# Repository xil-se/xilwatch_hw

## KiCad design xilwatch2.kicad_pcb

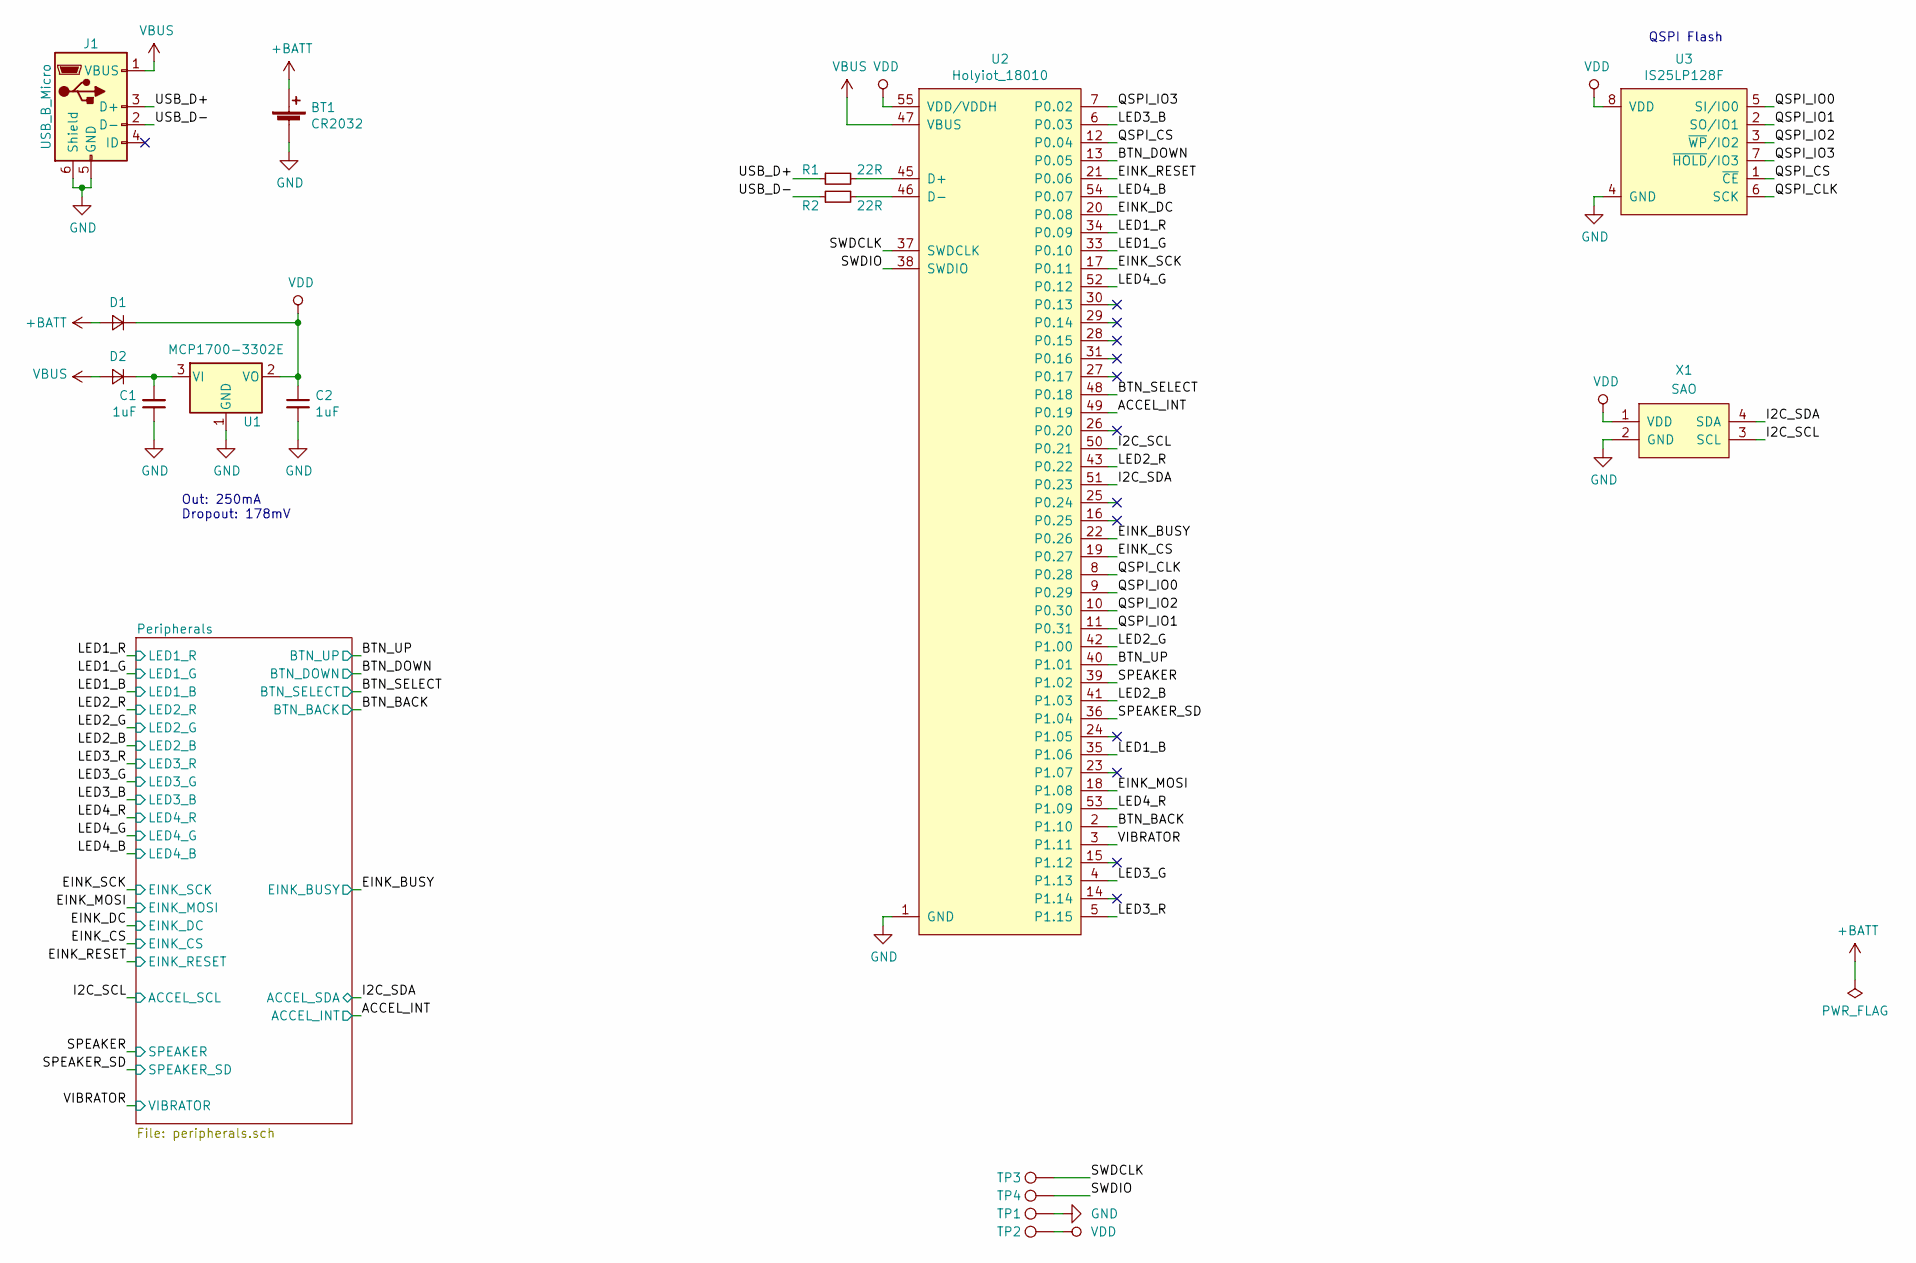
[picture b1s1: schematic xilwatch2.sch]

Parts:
BT1: CR2032; BAT-HLD-001
C1, C2: 1uF; C_0603_1608Metric
D1, D2: S1JHE; D_SOD-323F
J1: USB_B_Micro; USB_Micro-B_Molex-105017-0001
R1, R2: 22R; R_0603_1608Metric
TP1: TP_GND; TestPoint_Pad_D1.0mm
TP2: TP_VDD; TestPoint_Pad_D1.0mm
TP3: TP_SWDCLK; TestPoint_Pad_D1.0mm
TP4: TP_SWDIO; TestPoint_Pad_D1.0mm
U1: MCP1700-3302E; SOT-23
U2: Holyiot_18010
U3: IS25LP128F; WSON-8-1EP_6x5mm_P1.27mm_EP3.4x4mm
X1: SAO; SAO-2x2

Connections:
+BATT: BT1.1 (+), D1.2 (A)
/ACCEL_INT: U2.49 (P0.19); also elsewhere on the board
/BTN_BACK: U2.2 (P1.10); also elsewhere on the board
/BTN_DOWN: U2.13 (P0.05); also elsewhere on the board
/BTN_SELECT: U2.48 (P0.18); also elsewhere on the board
/BTN_UP: U2.40 (P1.01); also elsewhere on the board
/EINK_BUSY: U2.22 (P0.26); also elsewhere on the board
/EINK_CS: U2.19 (P0.27); also elsewhere on the board
/EINK_DC: U2.20 (P0.08); also elsewhere on the board
/EINK_MOSI: U2.18 (P1.08); also elsewhere on the board
/EINK_RESET: U2.21 (P0.06); also elsewhere on the board
/EINK_SCK: U2.17 (P0.11); also elsewhere on the board
/I2C_SCL: U2.50 (P0.21), X1.3 (SCL); also elsewhere on the board
/I2C_SDA: U2.51 (P0.23), X1.4 (SDA); also elsewhere on the board
/LED1_B: U2.35 (P1.06); also elsewhere on the board
/LED1_G: U2.33 (P0.10); also elsewhere on the board
/LED1_R: U2.34 (P0.09); also elsewhere on the board
/LED2_B: U2.41 (P1.03); also elsewhere on the board
/LED2_G: U2.42 (P1.00); also elsewhere on the board
/LED2_R: U2.43 (P0.22); also elsewhere on the board
/LED3_B: U2.6 (P0.03); also elsewhere on the board
/LED3_G: U2.4 (P1.13); also elsewhere on the board
/LED3_R: U2.5 (P1.15); also elsewhere on the board
/LED4_B: U2.54 (P0.07); also elsewhere on the board
/LED4_G: U2.52 (P0.12); also elsewhere on the board
/LED4_R: U2.53 (P1.09); also elsewhere on the board
/QSPI_CLK: U2.8 (P0.28), U3.6 (SCK)
/QSPI_CS: U2.12 (P0.04), U3.1 (~CE~)
/QSPI_IO0: U2.9 (P0.29), U3.5 (SI/IO0)
/QSPI_IO1: U2.11 (P0.31), U3.2 (SO/IO1)
/QSPI_IO2: U2.10 (P0.30), U3.3 (~WP~/IO2)
/QSPI_IO3: U2.7 (P0.02), U3.7 (~HOLD~/IO3)
/SPEAKER: U2.39 (P1.02); also elsewhere on the board
/SPEAKER_SD: U2.36 (P1.04); also elsewhere on the board
/SWDCLK: TP3.1, U2.37 (SWDCLK)
/SWDIO: TP4.1, U2.38 (SWDIO)
/USB_D+: J1.3 (D+), R1.1
/USB_D-: J1.2 (D-), R2.1
/VIBRATOR: U2.3 (P1.11); also elsewhere on the board
GND: BT1.2 (-), C1.1, C2.2, J1.5 (GND), J1.6 (Shield), TP1.1, U1.1 (GND), U2.1 (GND), U2.32 (GND), U2.44 (GND), U3.4 (GND), U3.9 (GND), X1.2 (GND); also elsewhere on the board
unnamed: C1.2, D2.1 (K), U1.3 (VI)
unnamed: R1.2, U2.45 (D+)
unnamed: R2.2, U2.46 (D-)
VBUS: D2.2 (A), J1.1 (VBUS), U2.47 (VBUS)
VDD: C2.1, D1.1 (K), TP2.1, U1.2 (VO), U2.55 (VDD/VDDH), U3.8 (VDD), X1.1 (VDD); also elsewhere on the board

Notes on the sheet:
Out: 250mA Dropout: 178mV
QSPI Flash

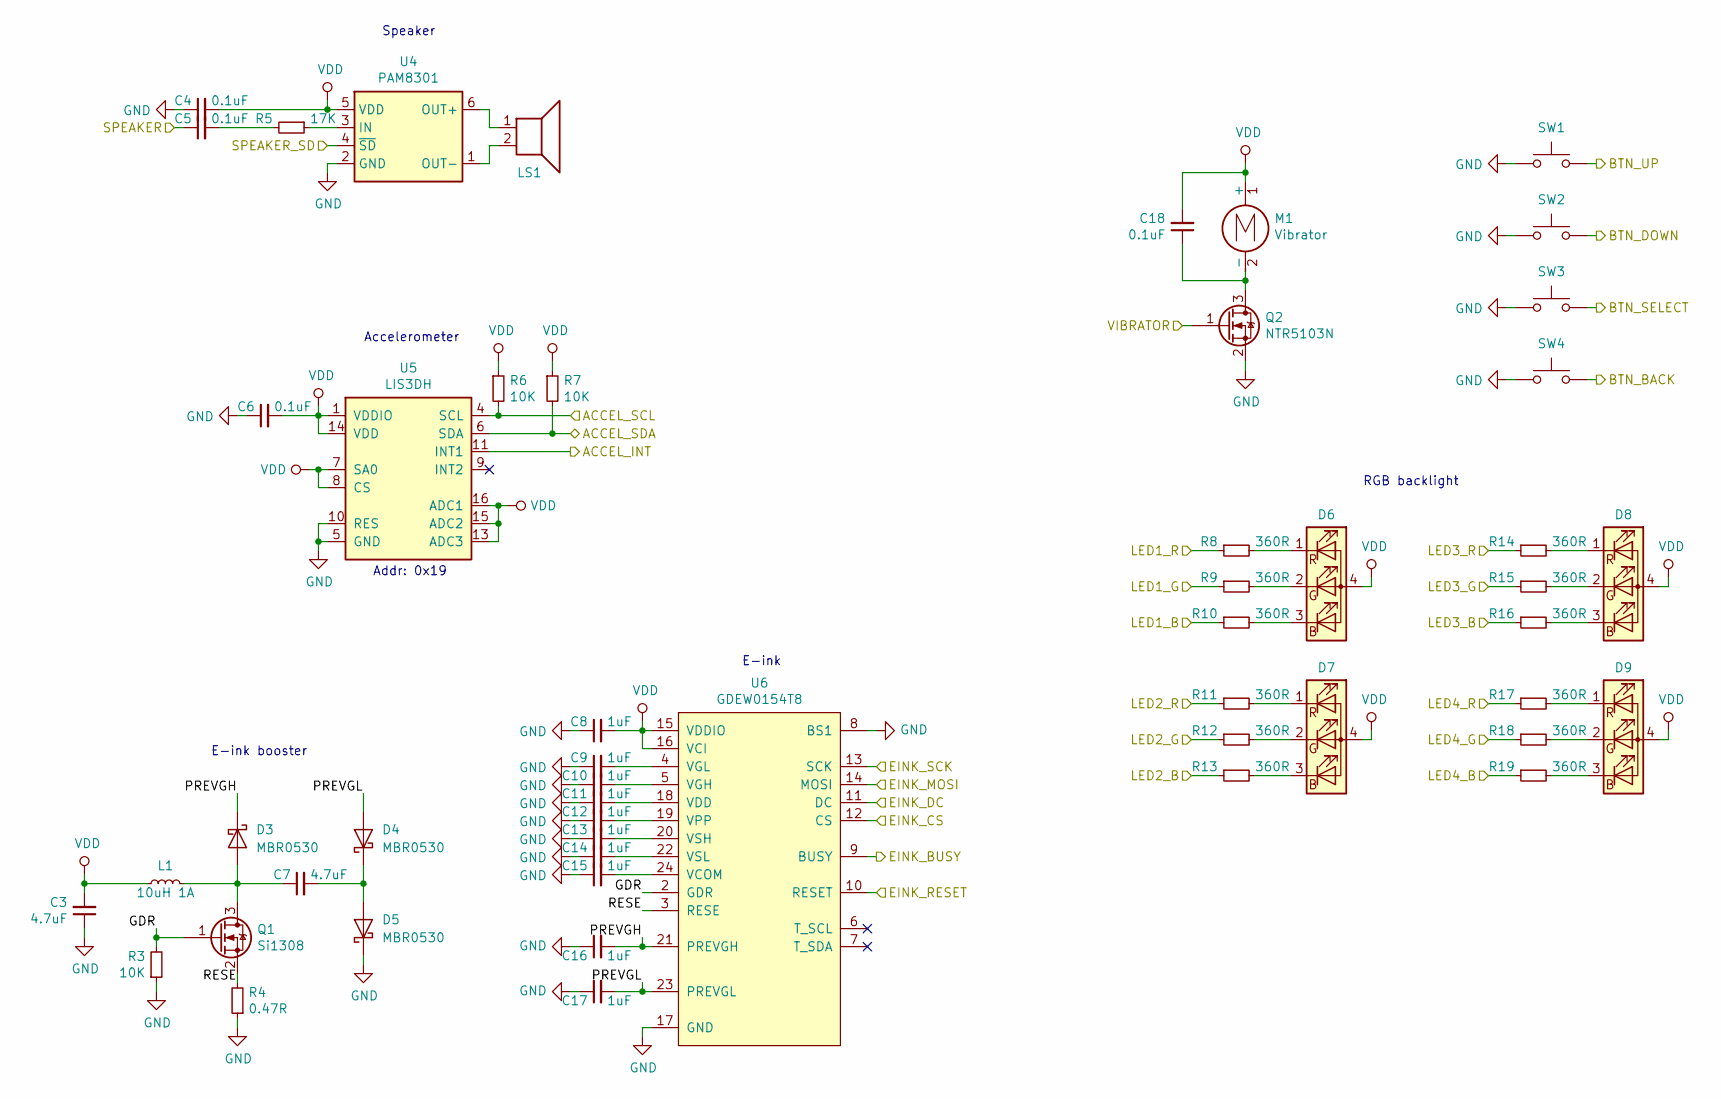
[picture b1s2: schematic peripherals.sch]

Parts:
C3, C7: 4.7uF; C_0603_1608Metric
C4, C5, C6, C18: 0.1uF; C_0603_1608Metric
C8, C9, C10, C11, C12, C13, C14, C15, C16, C17: 1uF; C_0603_1608Metric
D3, D4, D5: MBR0530; D_SOD-123
D6: LED_TopLeft; LED_RGBA_0606
D7: LED_TopRight; LED_RGBA_0606
D8: LED_BottomLeft; LED_RGBA_0606
D9: LED_BottomRight; LED_RGBA_0606
L1: 10uH 1A; L_Taiyo-Yuden_MD-3030; Part AISC-1210HS-100K-T2
LS1: CMT-5023S-SMT; CMT-5023S
M1: Vibrator; C1026B
Q1: Si1308; SOT-23
Q2: NTR5103N; SOT-23
R3, R6, R7: 10K; R_0603_1608Metric
R4: 0.47R; R_0603_1608Metric
R5: 17K; R_0603_1608Metric
R8, R9, R10, R11, R12, R13, R14, R15, R16, R17, R18, R19: 360R; R_0603_1608Metric
SW1: Btn_Up; KLS7-TS2402
SW2: Btn_Down; KLS7-TS2402
SW3: Btn_Select; KLS7-TS2402
SW4: Btn_Back; KLS7-TS2402
U4: PAM8301; SOT-23-6
U5: LIS3DH; LGA-16_3x3mm_P0.5mm_LayoutBorder3x5y
U6: GDEW0154T8; GoodDisplay_24P-0.5SH_1x24-Horizontal

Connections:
/ACCEL_INT: U5.11 (INT1); also elsewhere on the board
/BTN_BACK: SW4.2; also elsewhere on the board
/BTN_DOWN: SW2.2; also elsewhere on the board
/BTN_SELECT: SW3.2; also elsewhere on the board
/BTN_UP: SW1.2; also elsewhere on the board
/EINK_BUSY: U6.9 (BUSY); also elsewhere on the board
/EINK_CS: U6.12 (CS); also elsewhere on the board
/EINK_DC: U6.11 (DC); also elsewhere on the board
/EINK_MOSI: U6.14 (MOSI); also elsewhere on the board
/EINK_RESET: U6.10 (RESET); also elsewhere on the board
/EINK_SCK: U6.13 (SCK); also elsewhere on the board
/I2C_SCL: R6.2, U5.4 (SCL); also elsewhere on the board
/I2C_SDA: R7.2, U5.6 (SDA); also elsewhere on the board
/LED1_B: R10.1; also elsewhere on the board
/LED1_G: R9.1; also elsewhere on the board
/LED1_R: R8.1; also elsewhere on the board
/LED2_B: R13.1; also elsewhere on the board
/LED2_G: R12.1; also elsewhere on the board
/LED2_R: R11.1; also elsewhere on the board
/LED3_B: R16.1; also elsewhere on the board
/LED3_G: R15.1; also elsewhere on the board
/LED3_R: R14.1; also elsewhere on the board
/LED4_B: R19.1; also elsewhere on the board
/LED4_G: R18.1; also elsewhere on the board
/LED4_R: R17.1; also elsewhere on the board
/Peripherals/GDR: Q1.1 (G), R3.2, U6.2 (GDR)
/Peripherals/PREVGH: C16.2, D3.1 (K), U6.21 (PREVGH)
/Peripherals/PREVGL: C17.2, D4.2 (A), U6.23 (PREVGL)
/Peripherals/RESE: Q1.2 (S), R4.2, U6.3 (RESE)
/SPEAKER: C5.1; also elsewhere on the board
/SPEAKER_SD: U4.4 (~SD); also elsewhere on the board
/VIBRATOR: Q2.1 (G); also elsewhere on the board
GND: C3.1, C4.1, C6.1, C8.1, C9.1, C10.1, C11.1, C12.1, C13.1, C14.1, C15.1, C16.1, C17.1, D5.1 (K), Q2.2 (S), R3.1, R4.1, SW1.1, SW2.1, SW3.1, SW4.1, U4.2 (GND), U5.5 (GND), U5.10 (RES), U5.12 (GND), U6.8 (BS1), U6.17 (GND); also elsewhere on the board
unnamed: C5.2, R5.2
unnamed: C7.1, D3.2 (A), L1.1, Q1.3 (D)
unnamed: C7.2, D4.1 (K), D5.2 (A)
unnamed: C9.2, U6.4 (VGL)
unnamed: C10.2, U6.5 (VGH)
unnamed: C11.2, U6.18 (VDD)
unnamed: C12.2, U6.19 (VPP)
unnamed: C13.2, U6.20 (VSH)
unnamed: C14.2, U6.22 (VSL)
unnamed: C15.2, U6.24 (VCOM)
unnamed: C18.1, M1.2 (-), Q2.3 (D)
unnamed: D6.1 (RK), R8.2
unnamed: D6.2 (GK), R9.2
unnamed: D6.3 (BK), R10.2
unnamed: D7.1 (RK), R11.2
unnamed: D7.2 (GK), R12.2
unnamed: D7.3 (BK), R13.2
unnamed: D8.1 (RK), R14.2
unnamed: D8.2 (GK), R15.2
unnamed: D8.3 (BK), R16.2
unnamed: D9.1 (RK), R17.2
unnamed: D9.2 (GK), R18.2
unnamed: D9.3 (BK), R19.2
unnamed: LS1.1, U4.6 (OUT+)
unnamed: LS1.2, U4.1 (OUT-)
unnamed: R5.1, U4.3 (IN)
VDD: C3.2, C4.2, C6.2, C8.2, C18.2, D6.4 (A), D7.4 (A), D8.4 (A), D9.4 (A), L1.2, M1.1 (+), R6.1, R7.1, U4.5 (VDD), U5.1 (VDDIO), U5.7 (SA0), U5.8 (CS), U5.13 (ADC3), U5.14 (VDD), U5.15 (ADC2), U5.16 (ADC1), U6.15 (VDDIO), U6.16 (VCI); also elsewhere on the board

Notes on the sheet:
Speaker
E-ink
E-ink booster
Accelerometer
RGB backlight
Addr: 0x19

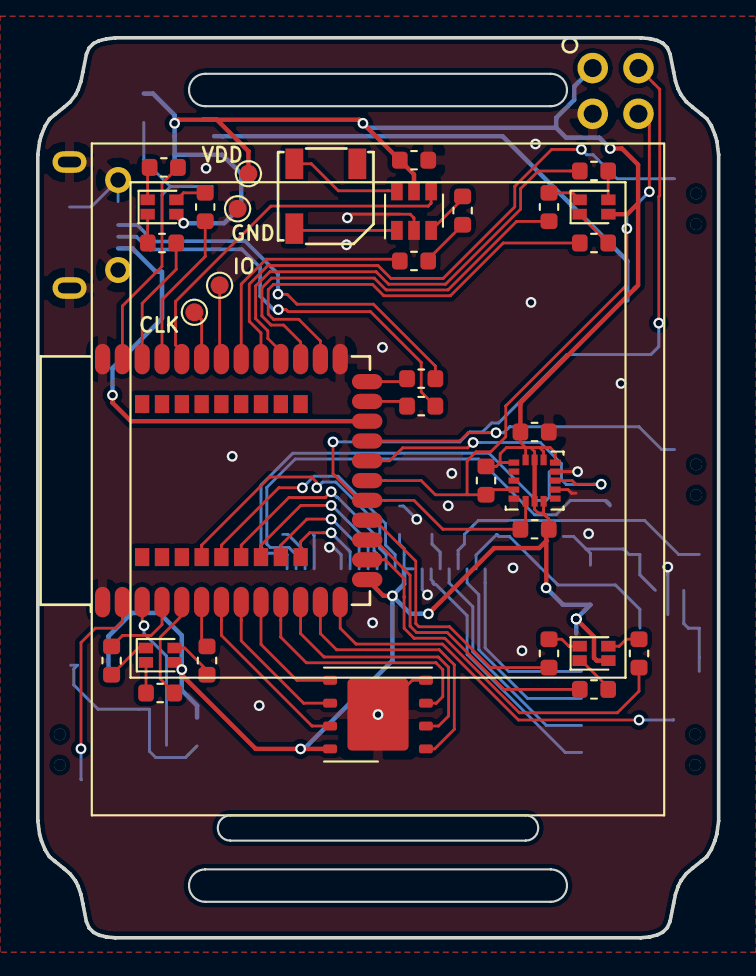
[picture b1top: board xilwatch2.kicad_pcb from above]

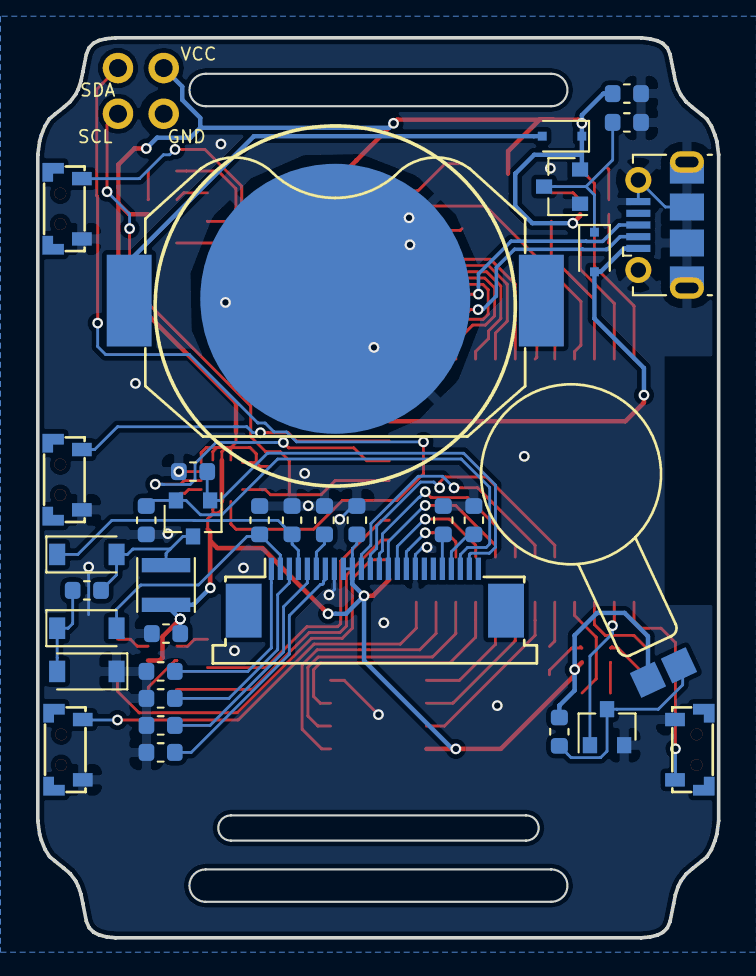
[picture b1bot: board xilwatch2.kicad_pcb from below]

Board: 2 copper layers, 37.8 x 50.0 mm, 68 parts (34 on the bottom side), 75 nets.

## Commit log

2018-09-14 Initial import
2018-09-14 More work, mostly copied from rev1
2018-09-14 Finish power, usb, replace accel, add flash and assign footprints
2018-09-17 Finish up the schematic
2018-09-18 Change of plans, now a nRF52840 with E-ink
2018-09-23 Finish rev1
